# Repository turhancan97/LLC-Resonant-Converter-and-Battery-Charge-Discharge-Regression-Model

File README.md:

# High Power Efficiency Design Approach of a LLC Resonant Converter for UPS Battery Charger Application and Battery Charge - Discharge Regression Model
## Turhan Can Kargın BACHELOR OF SCIENCE GRADUATION PROJECT

In this project, an optimal design procedure of inductor-inductor-capacitor (LLC) resonant DC-DC converter is developed for uninterruptible power supply (UPS) battery charge applications based on high power efficiency. The LLC resonant converters have many advantages such as high-power efficiency and less switching losses when compared with other converters features. It is also capable of operating in narrow switching frequency where zero voltage switching can be provided. The DC-DC converter with 400V input and 48V/3.1A output has been selected as an experimental setup. In order to reach optimal design of LLC resonant converter and required output values, switching frequency might be determined as above of resonance frequency, based on theoretical calculations and Power Electronics Simulation package program. The obtained maximum power efficiency with the proposed method was measured as 95.22%. Besides, charge-discharge models of the battery were obtained from the battery data obtained via deriving regression models with machine learning algorithms where battery electrical energy consumptions, battery status, and temperature data can be analyzed. R^2 score and root mean square error tests are performed for ten different regression models. Random forest regression is determined as the best model among regression models for the obtained data set. 

Keywords: Energy; UPS battery charge; LLC resonant converter; regression models

Video -> https://www.youtube.com/watch?v=KwHaqaDpCxg&t=8s

### Simulation

### Schematic

### PCB

### Model Comparison

### Random Forest Score After Optimization Code

### Regression Models Visualization

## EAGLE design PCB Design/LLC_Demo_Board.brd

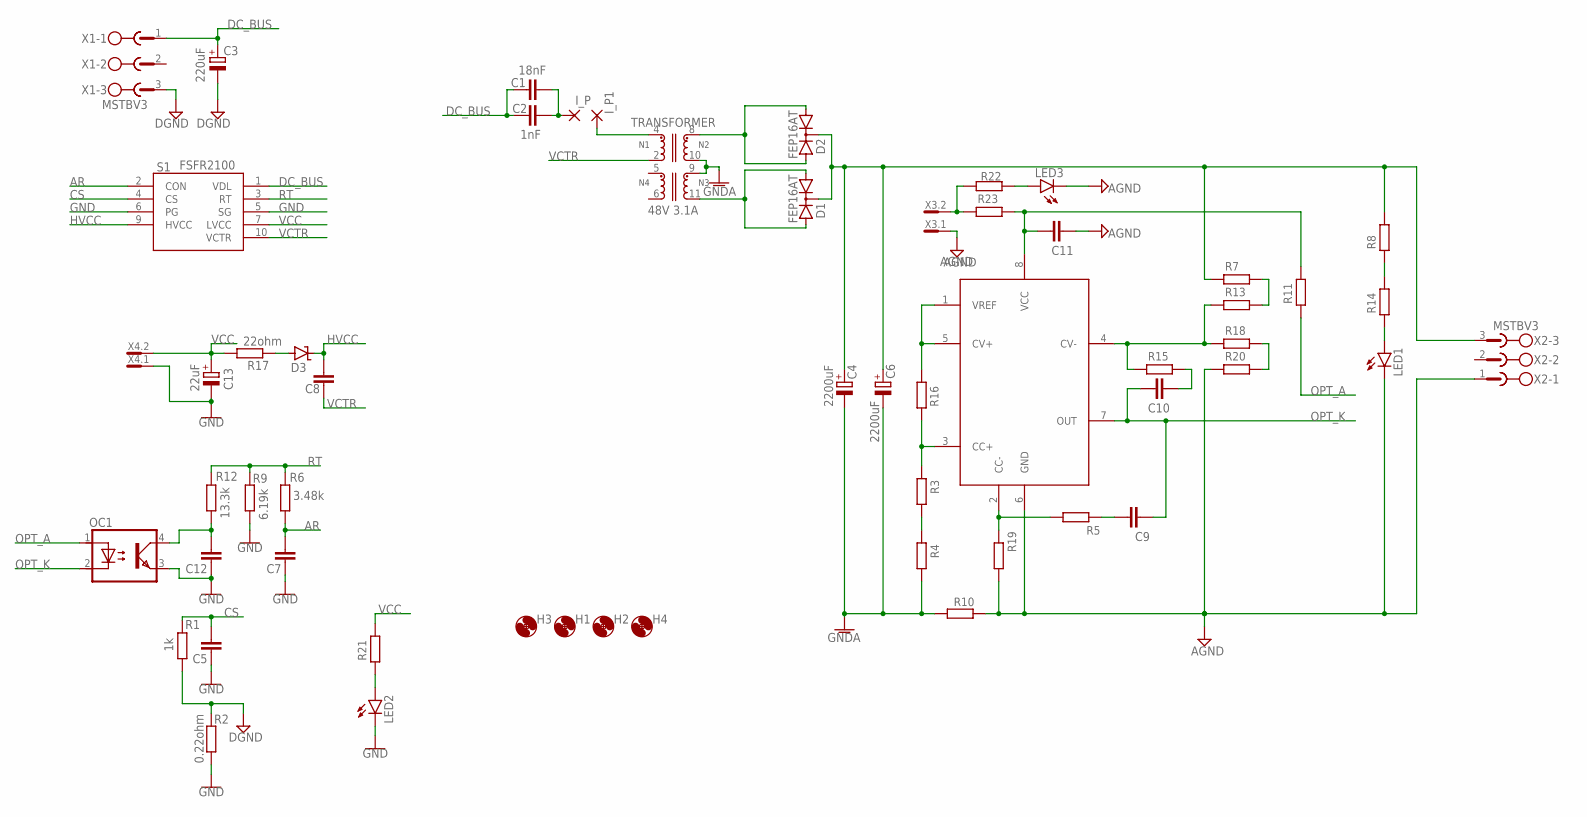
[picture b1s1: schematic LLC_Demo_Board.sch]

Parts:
C1: 18nF; C075-063X106
C2: 1nF; C150-072X183
C3: 220uF; EB30D
C4, C6: 2200uF; E7,5-18
C5: 100pF; C0805
C7: 220nF; C0805
C8: 150nF; C1206
C9, C10: 2.2nF; C1206
C11: 22uF; C0805
C12: 12nF; C0805
C13: 22uF; 153CLV-0605
D1, D2: FEP16AT; TO220ABS
D3: SUPPRESSOR-SMBJ; SMBJ
H1, H2, H3, H4: MOUNT-HOLE4.1; 4,1
IC1: 1039-2224 / TSM1011ID SO-8 Constant Voltage and C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; SO-8
I_P, I_P1: 3,81/1,4
LED1, LED2, LED3: LED5MM
OC1: 1039-2189 / Opto coupler CEL-Renesas PS2561DL2-1Y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; PS2561DL2-1_OPTO
R1, R19: 1k; R0805
R2: 0.22ohm; R2512
R3, R4: 500ohm; R0805
R5, R15: 22k; R1206
R6: 3.48k; R0805
R7: 180k; R1206
R8, R14, R21, R22: 1029-3175 / RES 0805 22K %1; R1206
R9: 6.19k; R0805
R10: 50m; R2512
R11: 100ohm; R1206
R12: 13.3k; R0805
R13: 12k; R1206
R16: 15k; R0805
R17: 22ohm; R0805
R18, R20: 4.99k; R1206
R23: 1k; R1206
S1: FSFR2100
TRANSFORMER: 48V 3.1A; WE-LLCR_ETD34
X1, X2: MSTBV3
X3, X4: İKİLİ MOLEX; MCV2

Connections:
AGND: C11.1, IC1.6 (GND), LED1.K (C), LED3.K (C), R10.2, R19.1, R20.2, X2.1, X3.1
AR: C7.1, R6.2, S1.2 (CON)
CS: C5.1, R1.2, S1.4 (CS)
DC_BUS: C1.1, C2.1, C3.+, S1.1 (VDL), X1.1
DGND: C3.-, R1.1, R2.2, X1.3
GND: C5.2, C7.2, C12.2, C13.-, LED2.K (C), OC1.3, R2.1, R9.2, S1.5 (SG), S1.6 (PG), X4.1
GNDA: C4.-, C6.-, R4.1, R10.1, TRANSFORMER.9 (6), TRANSFORMER.10 (7)
HVCC: C8.1, D3.C, S1.9 (HVCC)
unnamed: R22.1, R23.2, X3.2
unnamed: C1.2, C2.2, I_P.1
unnamed: R8.2, R14.1
unnamed: D3.A, R17.1
unnamed: D1.A1, D1.A2, TRANSFORMER.11 (5)
unnamed: D2.A1, D2.A2, TRANSFORMER.8
unnamed: C12.1, OC1.4, R12.2
unnamed: LED2.A, R21.2
unnamed: LED1.A, R14.2
unnamed: LED3.A, R22.2
unnamed: I_P1.1, TRANSFORMER.4 (1)
unnamed: IC1.1 (VREF), IC1.5 (CV+), R16.2
unnamed: C9.2, R5.2
unnamed: C10.2, R15.2
unnamed: IC1.4 (CV-), R13.2, R15.1, R18.2
unnamed: IC1.2 (CC-), R5.1, R19.2
unnamed: IC1.3 (CC+), R3.2, R16.1
unnamed: C11.2, IC1.8 (VCC), R11.1, R23.1
unnamed: R18.1, R20.1
unnamed: R7.1, R13.1
unnamed: R3.1, R4.2
OPT_A: OC1.1, R11.2
OPT_K: C9.1, C10.1, IC1.7 (OUT), OC1.2
RT: R6.1, R9.1, R12.1, S1.3 (RT)
VCC: C13.+, R17.2, R21.1, S1.7 (LVCC), X4.2
VCTR: C8.2, S1.10 (VCTR), TRANSFORMER.2
VDC+: C4.+, C6.+, D1.C, D2.C, R7.2, R8.1, X2.3

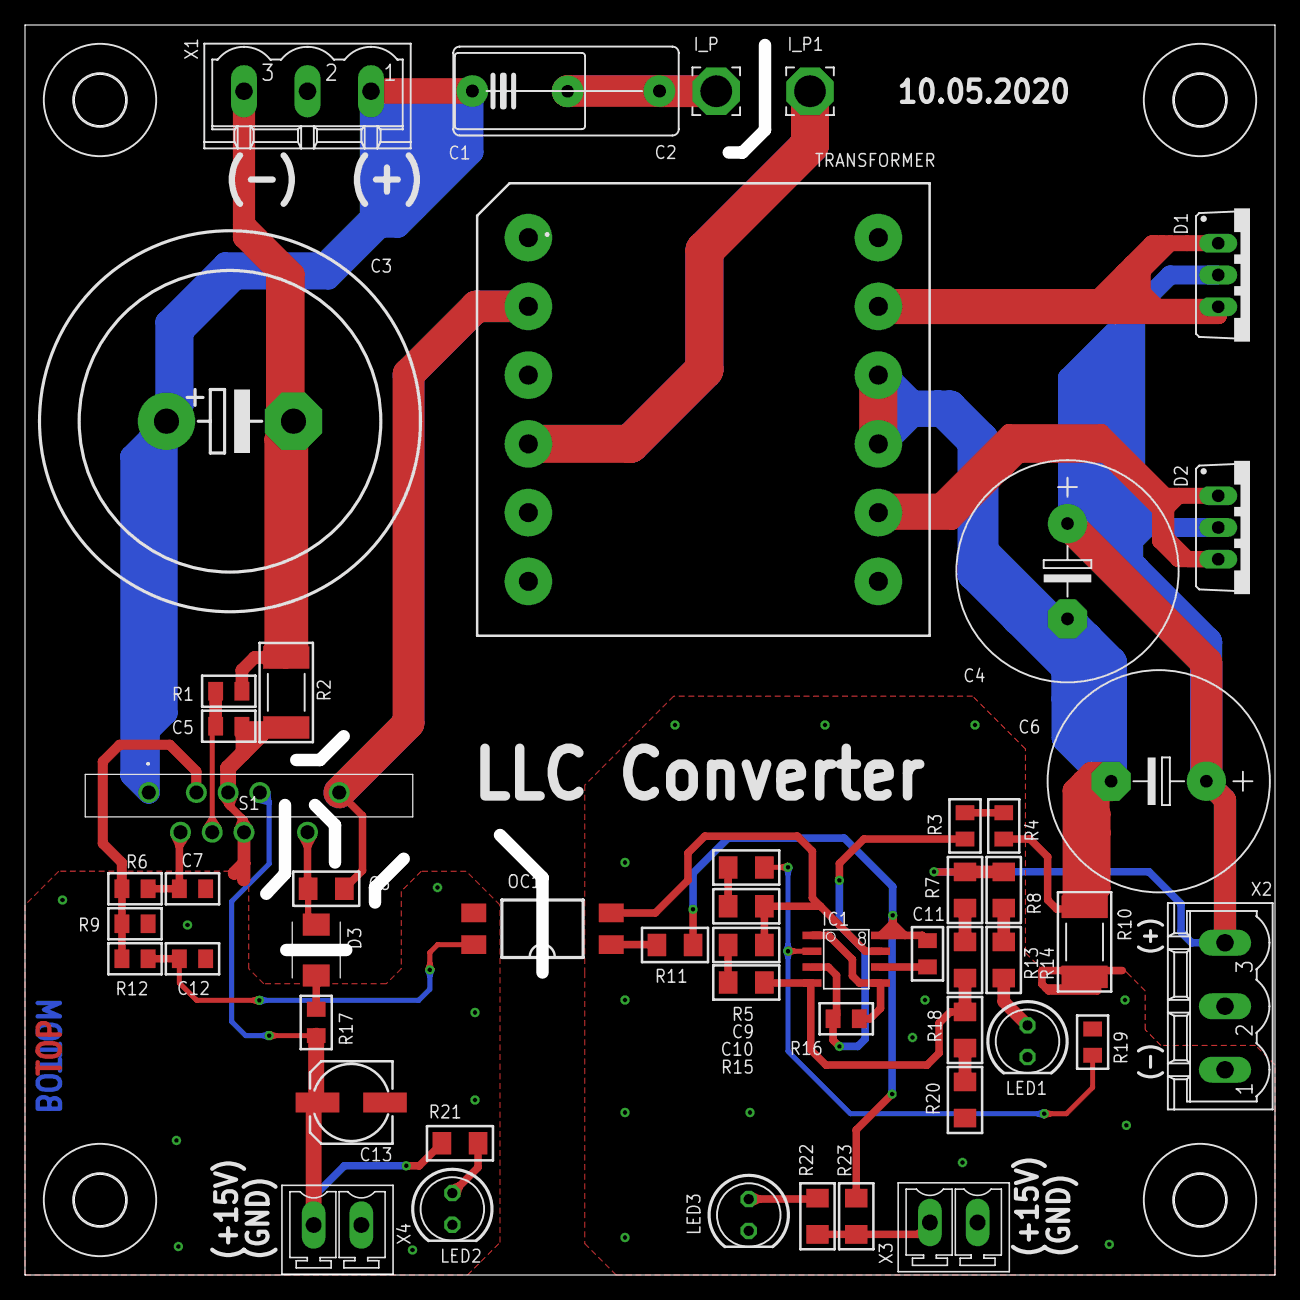
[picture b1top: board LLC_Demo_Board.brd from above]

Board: 2 copper layers, 99.0 x 99.0 mm, 56 parts (0 on the bottom side), 35 nets.

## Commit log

2020-06-25 new change
2020-06-25 folders
2020-06-25 change
2020-06-25 models
2020-06-25 model comparison
2020-06-26 reggression model change
2020-07-15 simulation matlab
2020-07-15 delete
2020-07-15 MATLAB Simulation
2020-07-16 book of abstract
2020-09-28 Article
2020-12-29 Book of Conference
2020-12-29 Conference Paper
2021-01-27 Rapor

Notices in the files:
parts and their libraries:
760895451_Eagle_WE-LLCR_rev19a: Copyright: Würth Elektronik
